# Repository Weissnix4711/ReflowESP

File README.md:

# ReflowESP

ESP32-WROOM-32 Reflow controller.

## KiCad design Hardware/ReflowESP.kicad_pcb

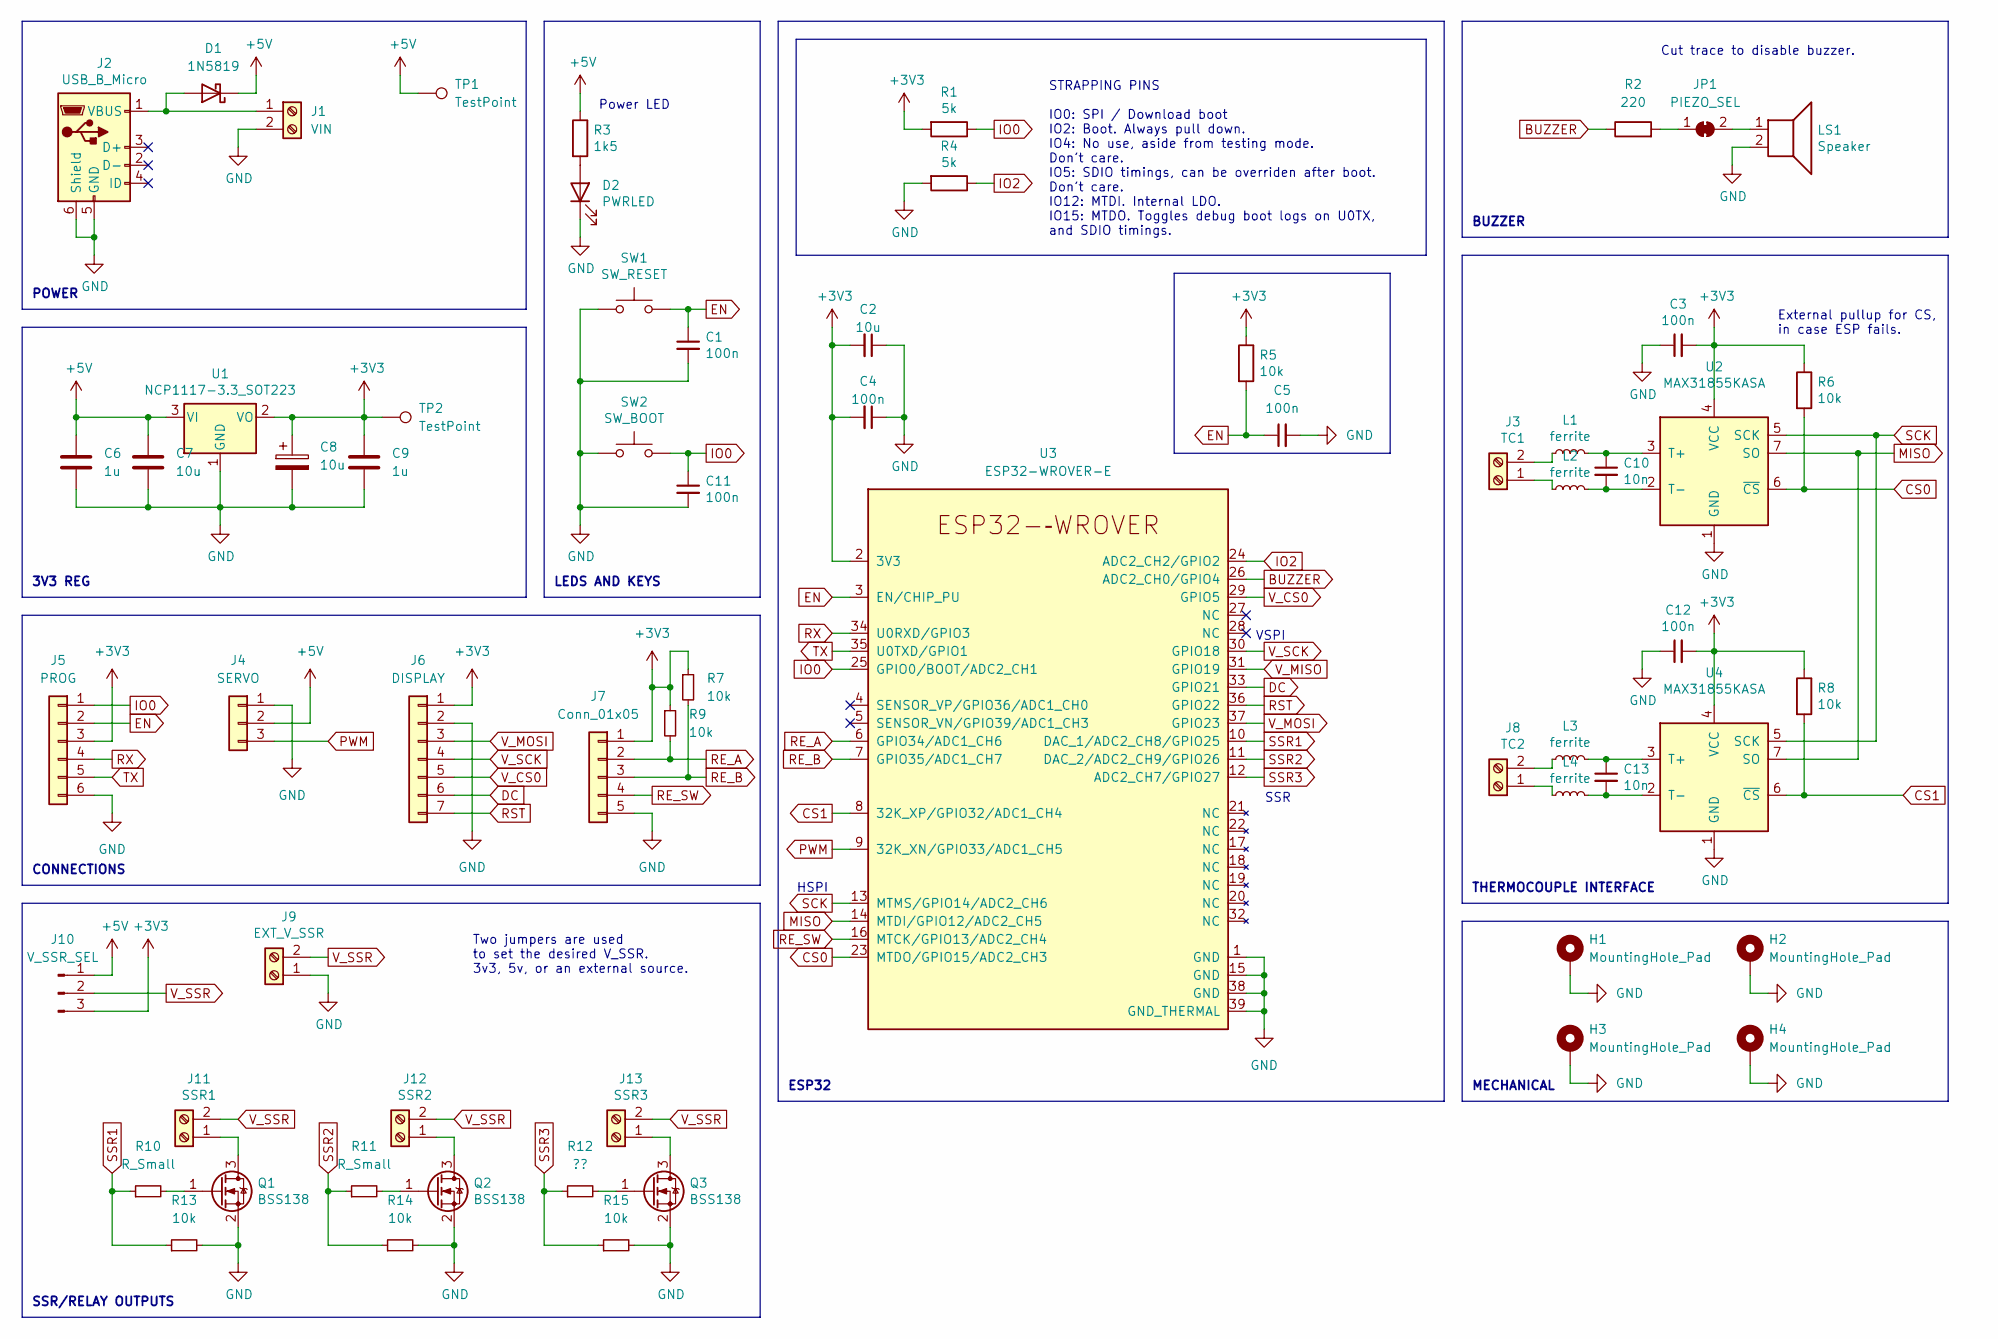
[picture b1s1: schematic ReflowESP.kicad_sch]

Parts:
C1, C3, C4, C5, C11, C12: 100n; C_0805_2012Metric
C2, C7: 10u; C_0805_2012Metric
C6, C9: 1u; C_0805_2012Metric
C8: 10u; CP_Elec_4x5.4
C10, C13: 10n; C_0805_2012Metric
D1: 1N5819; D_SOD-123
D2: PWRLED; LED_0805_2012Metric
H1, H2, H3, H4: MountingHole_Pad; MountingHole_3.2mm_M3_Pad
J1: VIN; TerminalBlock_KF301-2P
J2: USB_B_Micro; USB_Micro-B_Molex_47346-0001
J3: TC1; TerminalBlock_KF301-2P
J4: SERVO; PinHeader_1x03_P2.54mm_Horizontal
J5: PROG; PinHeader_1x06_P2.54mm_Vertical
J6: DISPLAY; PinHeader_1x07_P2.54mm_Horizontal
J7: Conn_01x05; PinHeader_1x05_P2.54mm_Vertical
J8: TC2; TerminalBlock_KF301-2P
J9: EXT_V_SSR; TerminalBlock_KF301-2P
J10: V_SSR_SEL; PinHeader_1x03_P2.54mm_Vertical
J11: SSR1; TerminalBlock_KF301-2P
J12: SSR2; TerminalBlock_KF301-2P
J13: SSR3; TerminalBlock_KF301-2P
JP1: PIEZO_SEL; SolderJumper-2_P1.3mm_Bridged_RoundedPad1.0x1.5mm
L1, L2, L3, L4: ferrite; L_0805_2012Metric
LS1: Speaker; MagneticBuzzer_ProSignal_ABI-010-RC
Q1, Q2, Q3: BSS138; SOT-23
R1, R4: 5k; R_0805_2012Metric
R2: 220; R_0805_2012Metric
R3: 1k5; R_0805_2012Metric
R5, R6, R7, R8, R9, R13, R14, R15: 10k; R_0805_2012Metric
R10, R11: R_Small; R_0805_2012Metric
R12: ??; R_0805_2012Metric
SW1: SW_RESET; SW_Push_SPST_NO_Alps_SKRK
SW2: SW_BOOT; SW_Push_SPST_NO_Alps_SKRK
TP1, TP2: TestPoint; TestPoint_Pad_D1.0mm
U1: NCP1117-3.3_SOT223; SOT-223-3_TabPin2
U2, U4: MAX31855KASA; SOIC-8_3.9x4.9mm_P1.27mm
U3: ESP32-WROVER-E

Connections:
+3V3: C2.2, C3.2, C4.2, C8.1, C9.1, C12.2, J5.3, J6.1, J7.1, J10.3, R1.2, R5.1, R6.1, R7.1, R8.1, R9.1, TP2.1, U1.2 (VO), U2.4 (VCC), U3.2 (3V3), U4.4 (VCC)
+5V: C6.1, C7.1, D1.1 (K), J4.2, J10.1, R3.1, TP1.1, U1.3 (VI)
BUZZER: R2.1, U3.26 (ADC2_CH0/GPIO4)
CS0: R6.2, U2.6 (~CS), U3.23 (MTDO/GPIO15/ADC2_CH3)
CS1: R8.2, U3.8 (32K_XP/GPIO32/ADC1_CH4), U4.6 (~CS)
DC: J6.6, U3.33 (GPIO21)
EN: C1.1, C5.1, J5.2, R5.2, SW1.2, U3.3 (EN/CHIP_PU)
GND: C1.2, C2.1, C3.1, C4.1, C5.2, C6.2, C7.2, C8.2, C9.2, C11.2, C12.1, D2.1 (K), H1.1, H2.1, H3.1, H4.1, J1.2, J2.5 (GND), J2.6 (Shield), J4.1, J5.6, J6.2, J7.5, J9.1, LS1.2, Q1.2 (S), Q2.2 (S), Q3.2 (S), R4.2, R13.2, R14.2, R15.2, SW1.1, SW2.1, U1.1 (GND), U2.1 (GND), U3.1 (GND), U3.15 (GND), U3.38 (GND), U3.39 (GND_THERMAL), U4.1 (GND)
IO0: C11.1, J5.1, R1.1, SW2.2, U3.25 (GPIO0/BOOT/ADC2_CH1)
IO2: R4.1, U3.24 (ADC2_CH2/GPIO2)
MISO: U2.7 (SO), U3.14 (MTDI/GPIO12/ADC2_CH5), U4.7 (SO)
unnamed: C10.1, L1.2, U2.3 (T+)
unnamed: C10.2, L2.2, U2.2 (T-)
unnamed: C13.1, L3.2, U4.3 (T+)
unnamed: C13.2, L4.2, U4.2 (T-)
unnamed: D1.2 (A), J1.1, J2.1 (VBUS)
unnamed: D2.2 (A), R3.2
unnamed: J3.1, L2.1
unnamed: J3.2, L1.1
unnamed: J8.1, L4.1
unnamed: J8.2, L3.1
unnamed: J11.1, Q1.3 (D)
unnamed: J12.1, Q2.3 (D)
unnamed: J13.1, Q3.3 (D)
unnamed: JP1.1 (A), R2.2
unnamed: JP1.2 (B), LS1.1
unnamed: Q1.1 (G), R10.2
unnamed: Q2.1 (G), R11.2
unnamed: Q3.1 (G), R12.2
PWM: J4.3, U3.9 (32K_XN/GPIO33/ADC1_CH5)
RE_A: J7.2, R9.2, U3.6 (GPIO34/ADC1_CH6)
RE_B: J7.3, R7.2, U3.7 (GPIO35/ADC1_CH7)
RE_SW: J7.4, U3.16 (MTCK/GPIO13/ADC2_CH4)
RST: J6.7, U3.36 (GPIO22)
RX: J5.4, U3.34 (U0RXD/GPIO3)
SCK: U2.5 (SCK), U3.13 (MTMS/GPIO14/ADC2_CH6), U4.5 (SCK)
SSR1: R10.1, R13.1, U3.10 (DAC_1/ADC2_CH8/GPIO25)
SSR2: R11.1, R14.1, U3.11 (DAC_2/ADC2_CH9/GPIO26)
SSR3: R12.1, R15.1, U3.12 (ADC2_CH7/GPIO27)
TX: J5.5, U3.35 (U0TXD/GPIO1)
V_CS0: J6.5, U3.29 (GPIO5)
V_MISO: U3.31 (GPIO19)
V_MOSI: J6.3, U3.37 (GPIO23)
V_SCK: J6.4, U3.30 (GPIO18)
V_SSR: J9.2, J10.2, J11.2, J12.2, J13.2

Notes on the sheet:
STRAPPING PINS IO0: SPI / Download boot IO2: Boot. Always pull down. IO4: No use, aside from testing mode. Don't care. IO5: SDIO timings, can be overriden after boot. Don't care. IO12: MTDI. Internal LDO. IO15: MTDO. Toggles debug boot logs on U0TX, and SDIO timings.
THERMOCOUPLE INTERFACE
Power LED
VSPI
POWER
Two jumpers are used to set the desired V_SSR. 3v3, 5v, or an external source.
3V3 REG
SSR/RELAY OUTPUTS
BUZZER
SSR
External pullup for CS, in case ESP fails.
MECHANICAL
Cut trace to disable buzzer.
ESP32
CONNECTIONS
LEDS AND KEYS
HSPI

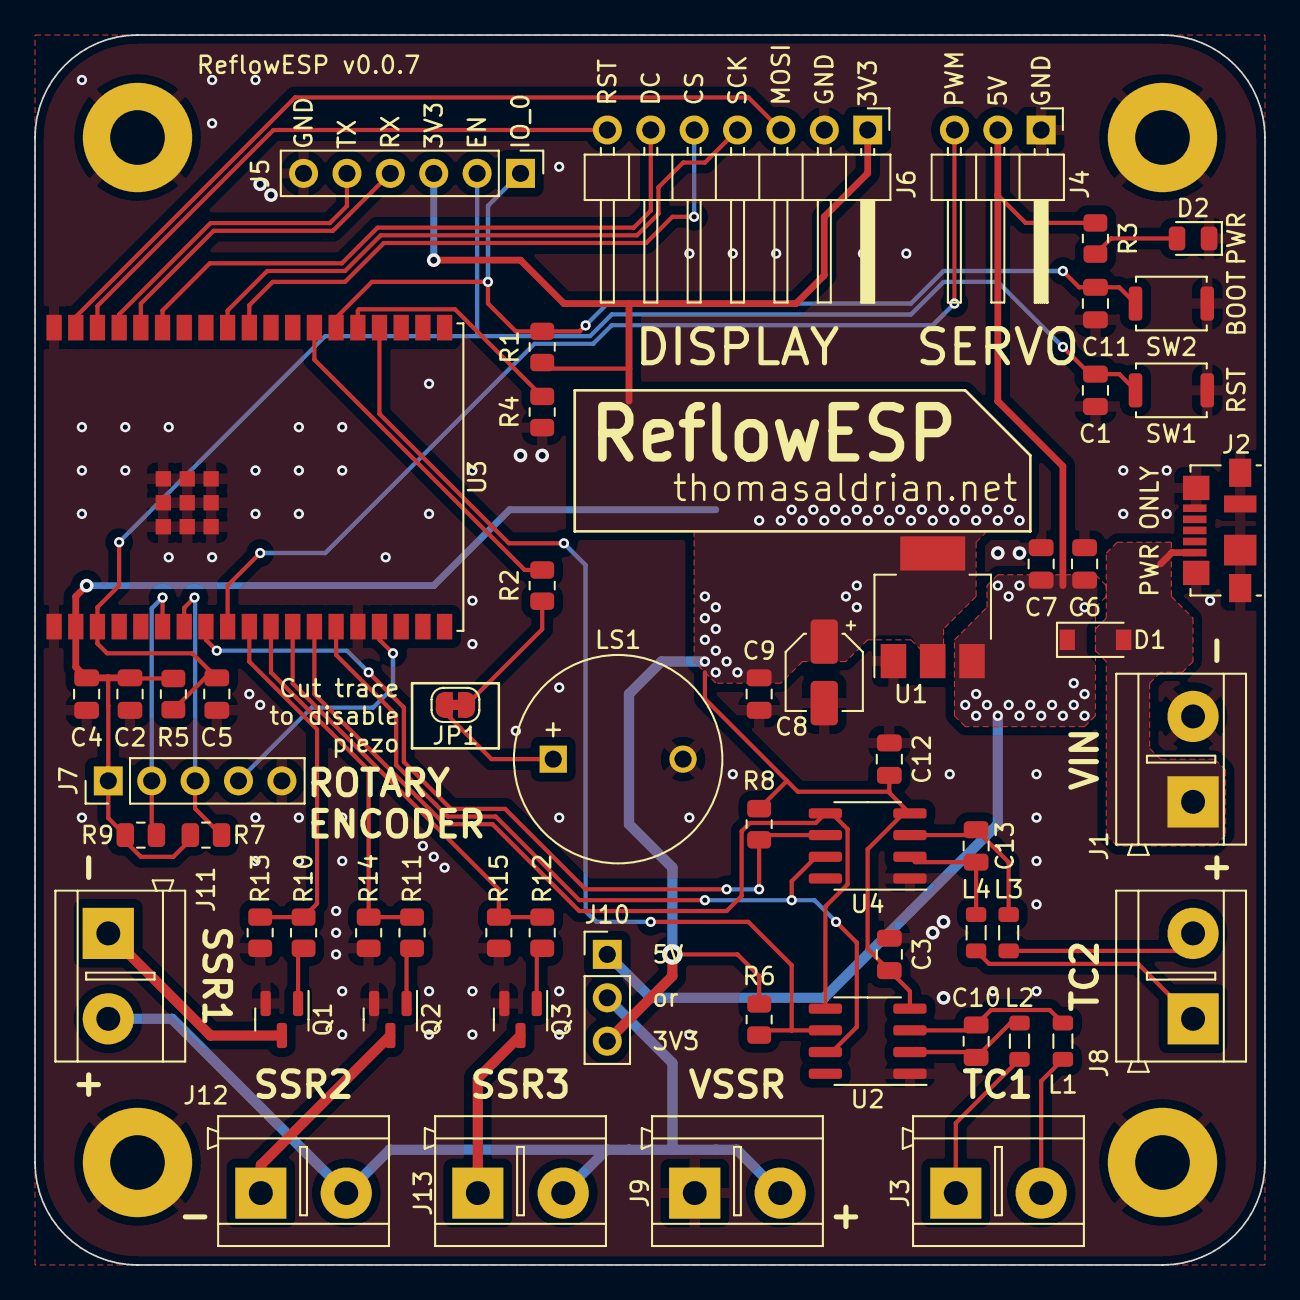
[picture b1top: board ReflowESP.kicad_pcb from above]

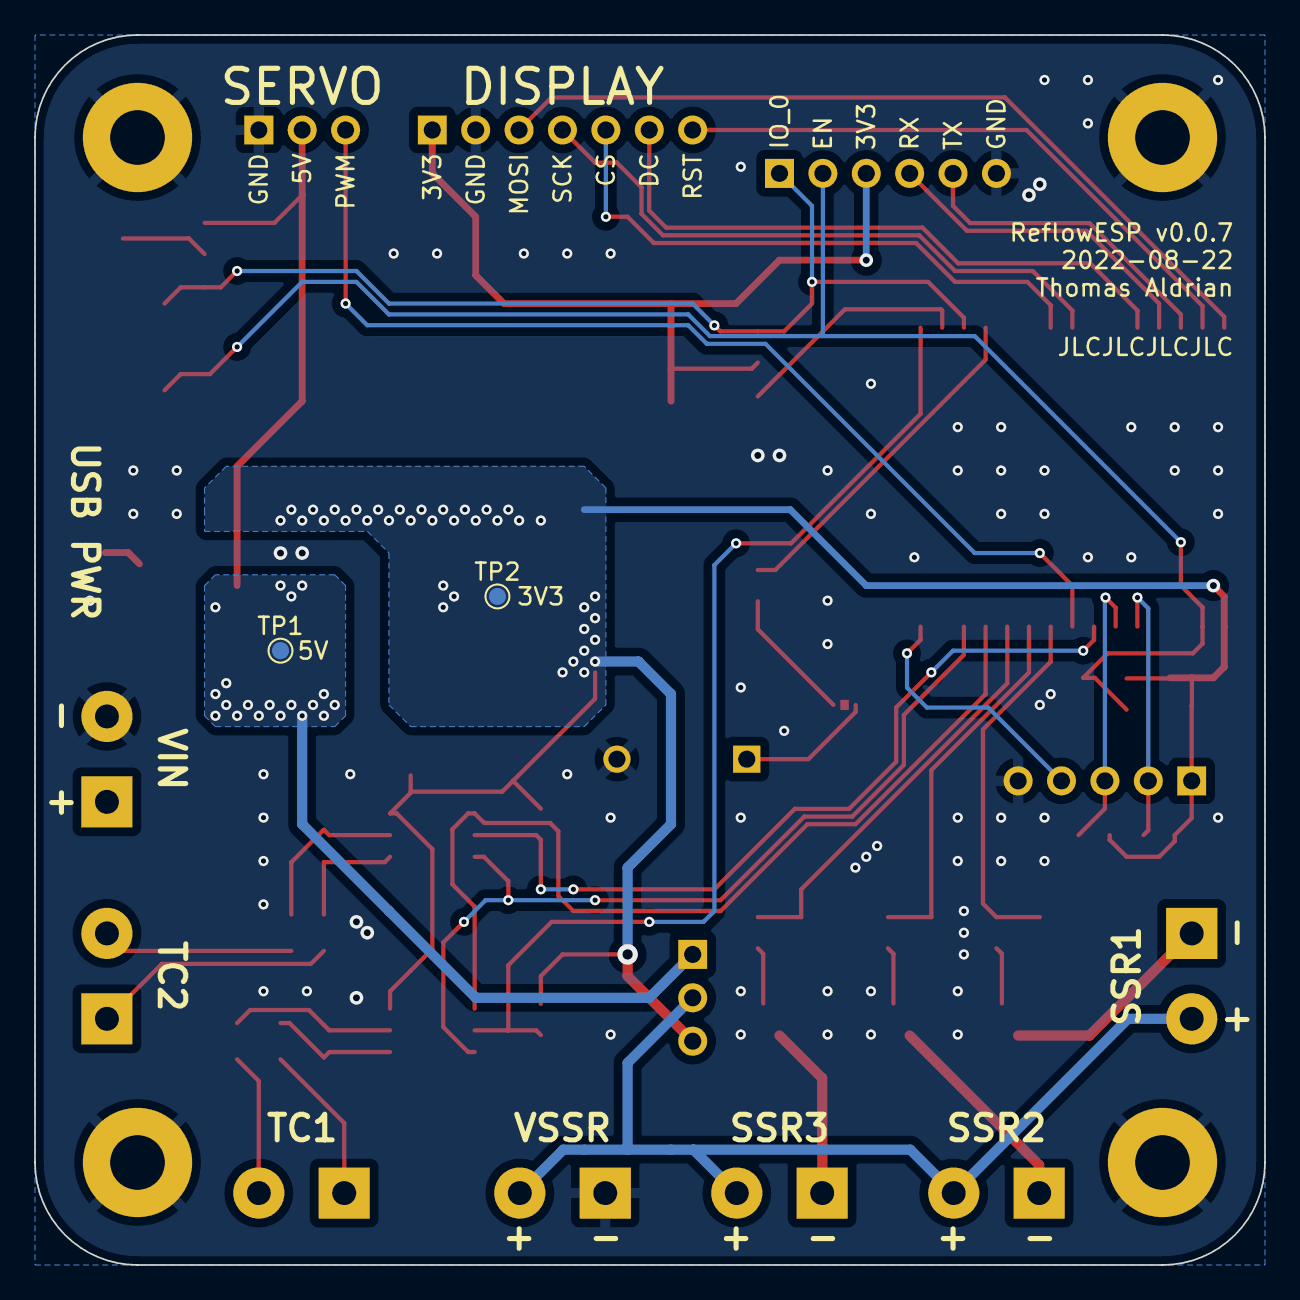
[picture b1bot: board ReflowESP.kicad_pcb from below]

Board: 2 copper layers, 72.0 x 72.0 mm, 64 parts (2 on the bottom side), 44 nets.

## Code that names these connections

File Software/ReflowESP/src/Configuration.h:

#pragma once

// @section info

#define MACHINE_NAME "ReflowESP"

// @section therm

/**
 * Thermocouple Interface
 *
 * Configure one of HAS_MAX6675 and HAS_MAX31855,
 * then configure pins below.
 */
// #define HAS_MAX31855
#define HAS_MAX6675

#define THERM_MISO 12
#define THERM_SCK 14

#define THERM_CS0 15
#define THERM_CS1 32

#define THERM_POLL_PERIOD 500

// Default PID values
#define PID_KP 0
#define PID_KI 0
#define PID_KD 0

// @section pins

// Buzzer pin
#define BUZZ 4

/**
 * SSR Outputs
 *
 * Define pins for SSR outputs here. Must define at least one.
 */
#define SSR1 25
#define SSR2 26

#define PWM_PERIOD 1000

// @section menu

// MAX DEPTH
// #define MAX_DEPTH 2
#define MAX_DEPTH 30

/**
 * LCD / OLED settings
 *
 * Must define all.
 */
#define FONT_WIDTH 6
#define FONT_HEIGHT 9
#define GFX_WIDTH 128
#define GFX_HEIGHT 128

/**
 * Rotary Encoder
 *
 * Must define all ENCA, ENCB, ENCBTN and ENCSTEPS.
 */
#define ENCA 34
#define ENCB 35
#define ENCBTN 13
#define ENCSTEPS 2

// Encoder decoder.
// :[ENC_NORMAL,ENC_FLAKY]
// #define ENC_DECODER ENC_FLAKY
#define ENC_DECODER ENC_NORMAL

// Additional options for ENC_FLAKY
#if ENC_DECODER == ENC_FLAKY
  #define ENC_HALFSTEP 1
#endif

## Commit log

2022-07-10 Update for v0.0.2
    Migrate to KiCad 6
    Switch to WROVER-E module and update symbol
    Mechanical components
2022-07-10 KiCad 6 gitignore
2022-07-10 Fix V_SSR_SEL
2022-07-11 Small tweaks for v0.0.4
    Remove USB-UART
    Add connections for programming, display and servo
    Add gate resistor for SSRs
    More filter caps for 3v3
    Update refs and footprints
    Fix symbol for ESP32 module
2022-07-14 Add screw terminal footprint
2022-07-14 Mostly finished layout
2022-07-24 Update schematic symbols for connectors
2022-07-24 Bump version
2022-07-24 Update PCB
    Add pin 1 marker for U3 and U4
    Add pinout for J4 and J5 to back silkscreen
    Remove hole part designators
2022-07-24 Get DRC to shut up
2022-07-24 Add exported views
2022-08-22 Update v0.0.7
    Add rotary encoder
2022-08-22 Add ibom
2023-01-27 Add profiles
2023-01-27 GPLv3
2023-01-27 Start work on firmware
2023-01-27 Add modified ClickEncoder lib
2023-01-27 Add root gitignore
2023-01-27 PCB Renders
    Preliminary. Need to fixup hardware.
2023-01-28 Thermocouple interface beginnings
2023-01-28 Small fixes
    Rename DISABLED macro to NENABLED to avoid redefinition.
    Style fixes.
2023-02-20 Add updated ibom
    Non-final.
